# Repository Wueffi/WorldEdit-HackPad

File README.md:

# WorldEdit Hackpad

The WorldEdit Hackpad is a 15 key macropad designed to run [WorldEdit](https://modrinth.com/plugin/worldedit) Macros inside of Minecraft. It also includes 15 WS2812B LEDs to give each Key and Keygroup a different Backlight.

## Features:
- Sleek 3D-Printed Case
- 15 Cherry MX Keys, ordered in one 3x3 and two 1x3 Keygroups
- 15 WS2812B RGB LEDs to give the keys a Backlight.
- Seeed Studio XIAO RP2040 Microcontroller

## CAD Model:
Everything holds together using 4 M3 Bolts and heatset inserts in each 4 corners of the case.

Disassembled

Assembled

## PCB
Schematic

PCB

I have decided to not use diodes, since I want to only press one button at a time and thus not have to care about ghosting. It also is easier to wire, fit and looks more aesthetic.

## Firmware
This hackpad uses [QMK](https://qmk.fm/) firmware. The Switches are encoded in a 4x3 Matrix

## BOM:
This is everything you need to make this HackPad!

- 1x XIAO RP2040
- 15x Cherry MX Switches
- 15x Keycaps
- 15x WS2812B LEDs
- 4x M3x5x4 Heatset inserts
- 4x M3x16mm SHCS Bolts
- 1x Case (Top and Bottom parts printed)

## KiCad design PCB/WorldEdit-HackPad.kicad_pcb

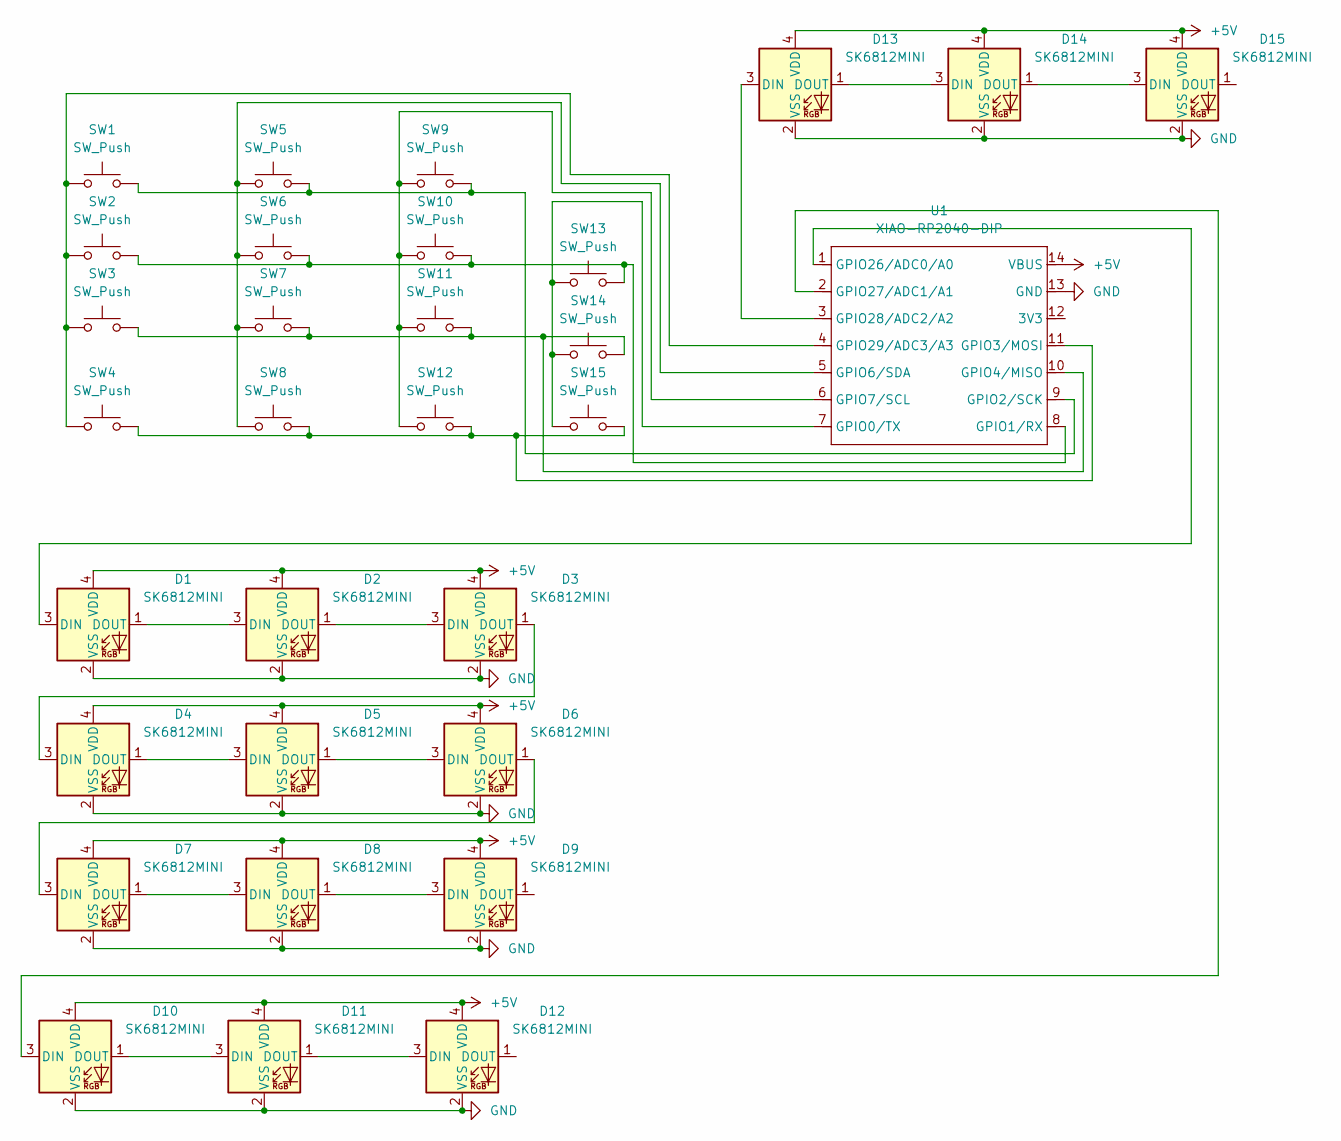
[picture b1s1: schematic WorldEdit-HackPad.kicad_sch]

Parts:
D1, D2, D3, D4, D5, D6, D7, D8, D9, D10, D11, D12, D13, D14, D15: SK6812MINI; LED_SK6812MINI_PLCC4_3.5x3.5mm_P1.75mm
SW1, SW2, SW3, SW4, SW5, SW6, SW7, SW8, SW9, SW10, SW11, SW12, SW13, SW14, SW15: SW_Push; SW_Cherry_MX_1.00u_PCB
U1: XIAO-RP2040-DIP

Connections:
+5V: D1.4 (VDD), D2.4 (VDD), D3.4 (VDD), D4.4 (VDD), D5.4 (VDD), D6.4 (VDD), D7.4 (VDD), D8.4 (VDD), D9.4 (VDD), D10.4 (VDD), D11.4 (VDD), D12.4 (VDD), D13.4 (VDD), D14.4 (VDD), D15.4 (VDD), U1.14 (VBUS)
GND: D1.2 (VSS), D2.2 (VSS), D3.2 (VSS), D4.2 (VSS), D5.2 (VSS), D6.2 (VSS), D7.2 (VSS), D8.2 (VSS), D9.2 (VSS), D10.2 (VSS), D11.2 (VSS), D12.2 (VSS), D13.2 (VSS), D14.2 (VSS), D15.2 (VSS), U1.13 (GND)
unnamed: D1.3 (DIN), U1.1 (GPIO26/ADC0/A0)
unnamed: D1.1 (DOUT), D2.3 (DIN)
unnamed: D2.1 (DOUT), D3.3 (DIN)
unnamed: D3.1 (DOUT), D4.3 (DIN)
unnamed: D4.1 (DOUT), D5.3 (DIN)
unnamed: D5.1 (DOUT), D6.3 (DIN)
unnamed: D6.1 (DOUT), D7.3 (DIN)
unnamed: D7.1 (DOUT), D8.3 (DIN)
unnamed: D8.1 (DOUT), D9.3 (DIN)
unnamed: D10.3 (DIN), U1.2 (GPIO27/ADC1/A1)
unnamed: D10.1 (DOUT), D11.3 (DIN)
unnamed: D11.1 (DOUT), D12.3 (DIN)
unnamed: D13.3 (DIN), U1.3 (GPIO28/ADC2/A2)
unnamed: D13.1 (DOUT), D14.3 (DIN)
unnamed: D14.1 (DOUT), D15.3 (DIN)
unnamed: SW13.1, SW14.1, SW15.1, U1.7 (GPIO0/TX)
unnamed: SW2.2, SW6.2, SW10.2, SW13.2, U1.8 (GPIO1/RX)
unnamed: SW1.2, SW5.2, SW9.2, U1.9 (GPIO2/SCK)
unnamed: SW4.2, SW8.2, SW12.2, SW15.2, U1.11 (GPIO3/MOSI)
unnamed: SW3.2, SW7.2, SW11.2, SW14.2, U1.10 (GPIO4/MISO)
unnamed: SW5.1, SW6.1, SW7.1, SW8.1, U1.5 (GPIO6/SDA)
unnamed: SW9.1, SW10.1, SW11.1, SW12.1, U1.6 (GPIO7/SCL)
unnamed: SW1.1, SW2.1, SW3.1, SW4.1, U1.4 (GPIO29/ADC3/A3)

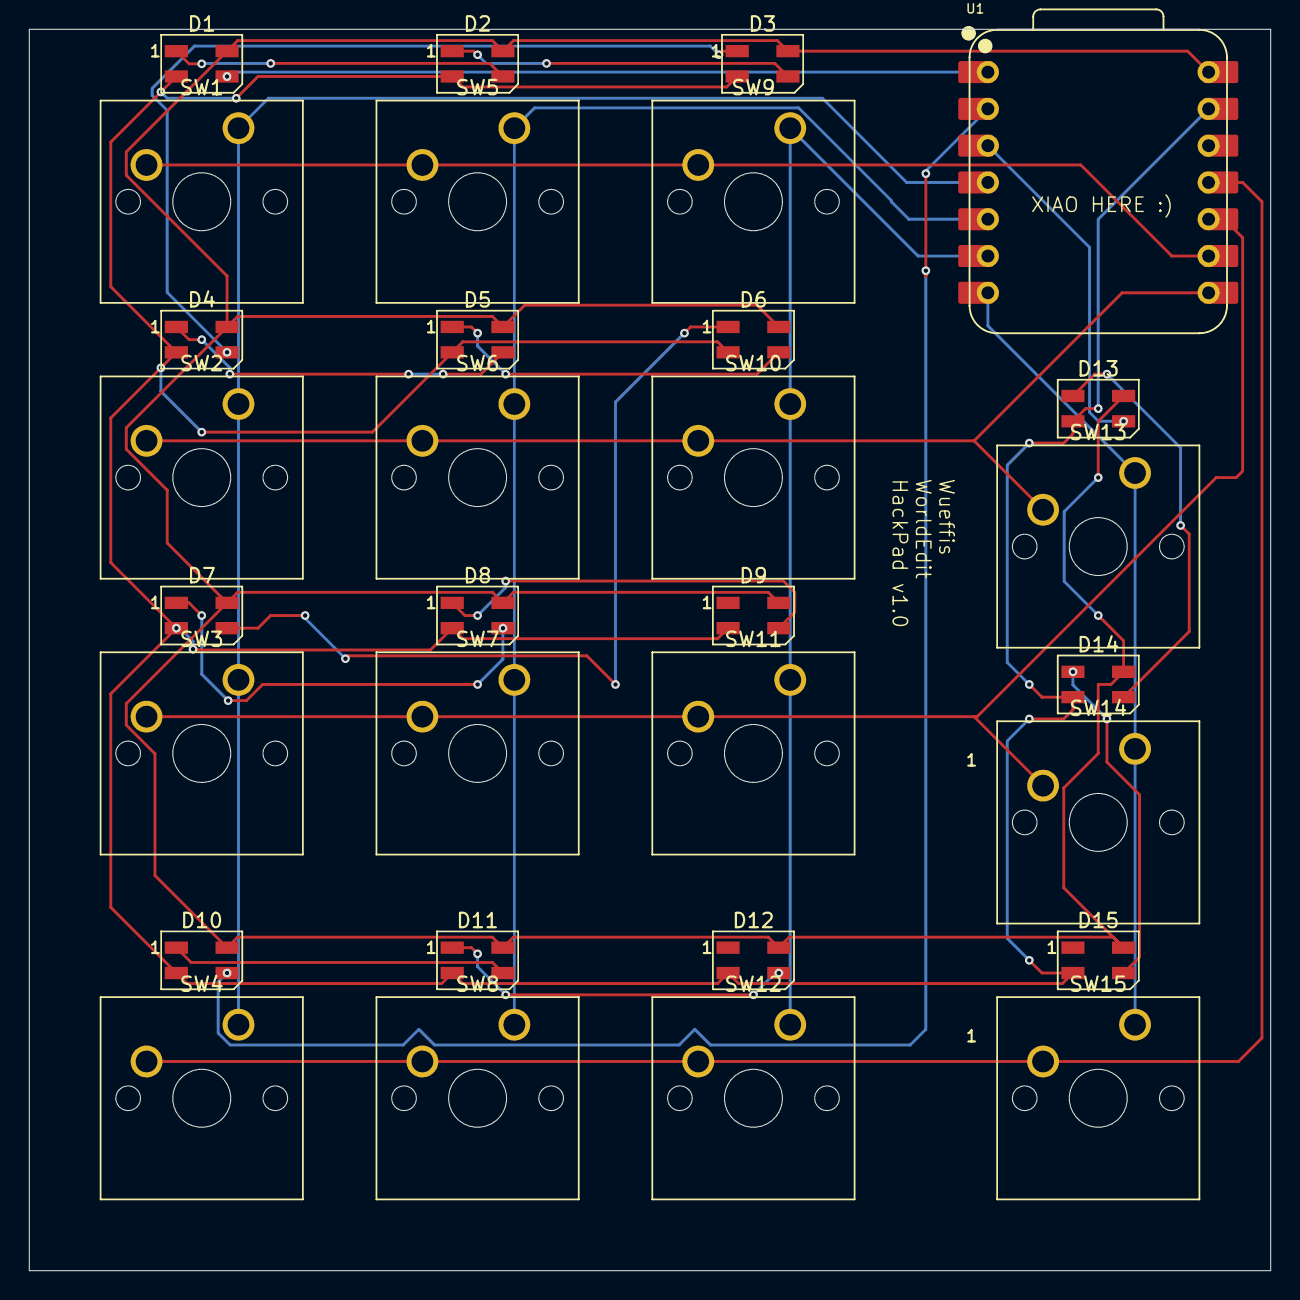
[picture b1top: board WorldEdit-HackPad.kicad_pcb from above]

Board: 2 copper layers, 85.7 x 85.7 mm, 31 parts (0 on the bottom side), 25 nets.

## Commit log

2025-12-26 Add CAD and PCB Files
2025-12-26 Update Schem and PCB
2025-12-26 Update Images
